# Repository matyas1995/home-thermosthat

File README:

What to do to get OpenThread running

OpenThread now runs in MCUXpresso project (at least the console does).

Next step is to get away from this Eclipse based crap and get the project working under Cmake (so all the way back to start).

MCUXpresso should only be needed to use the clock and peripheral configurators (They make quite a lot of things easier). These will then be just copied over.

The README of the mbedTLS library in the SDK mentions that it has been adapted to use the LTC crypto module of the chip. This should definitely be checked out to use hardware acceleration.

testchange3 for testcommit

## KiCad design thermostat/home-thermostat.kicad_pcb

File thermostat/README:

Errata: gate resistors on GPIO LED drivers missing. Will not pose great problems as long as switching frequency does not get too high to overload MCU pins.

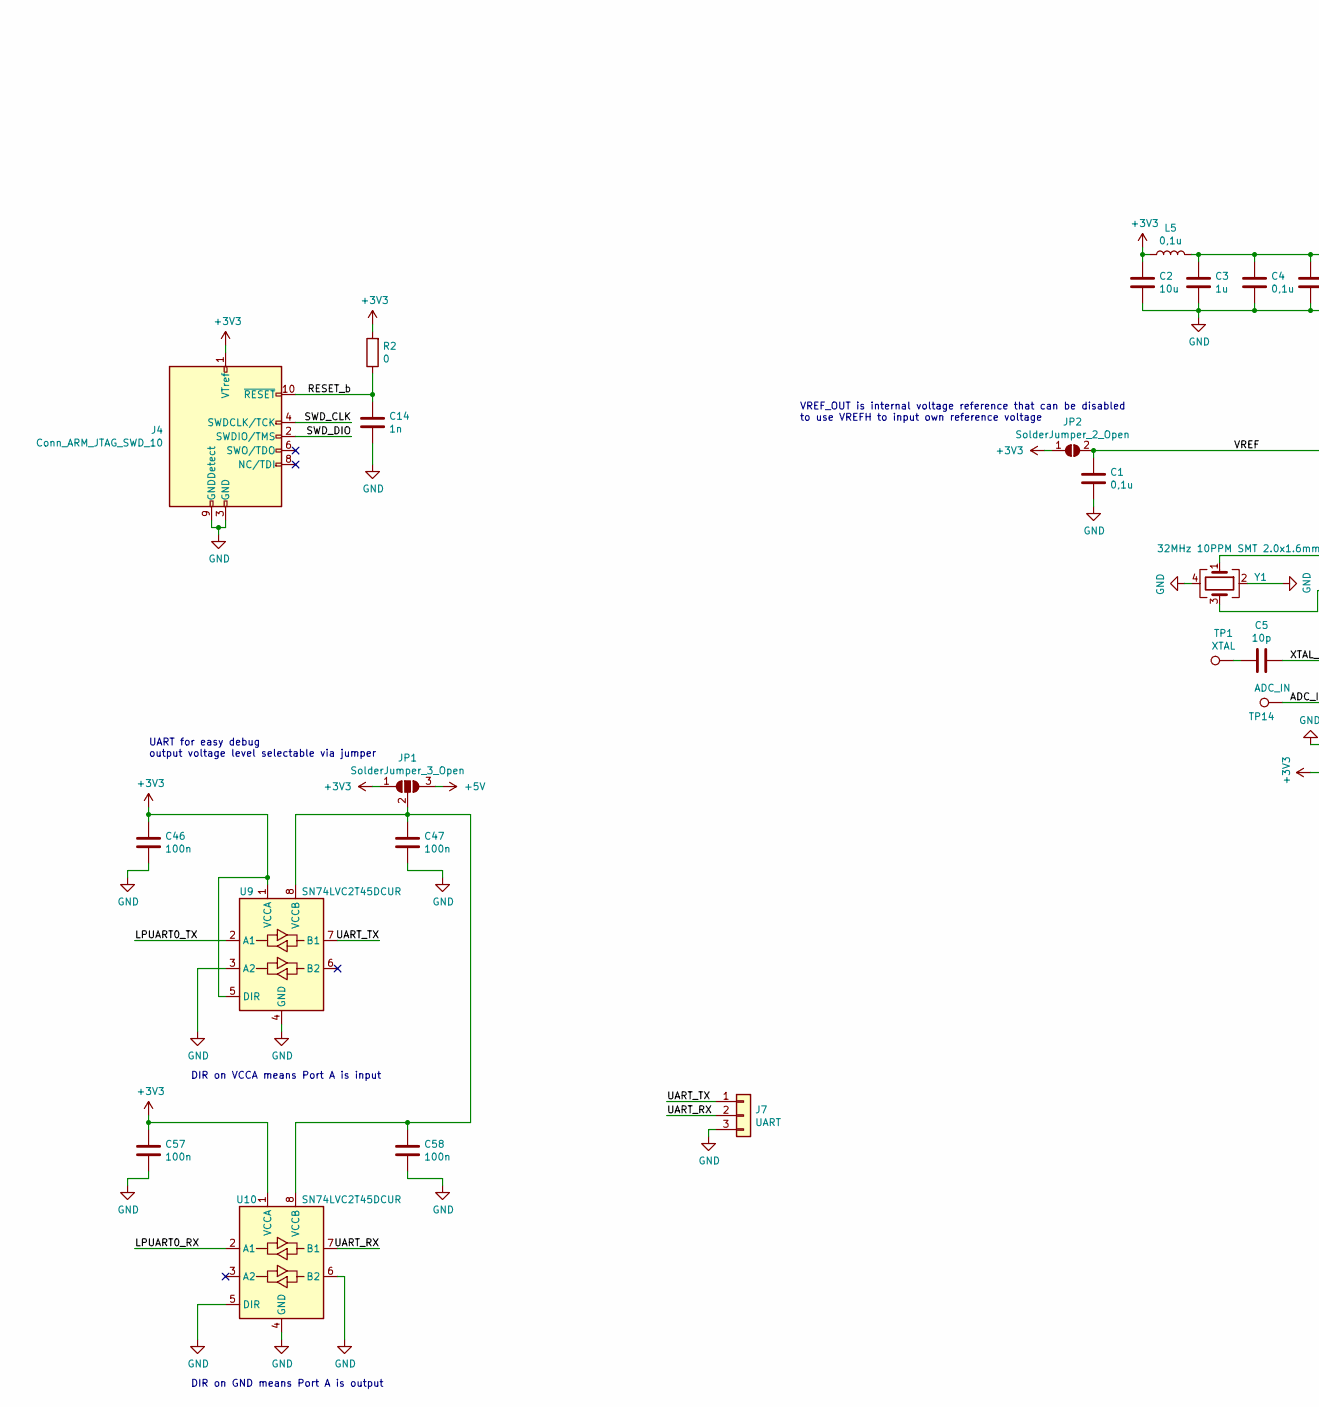
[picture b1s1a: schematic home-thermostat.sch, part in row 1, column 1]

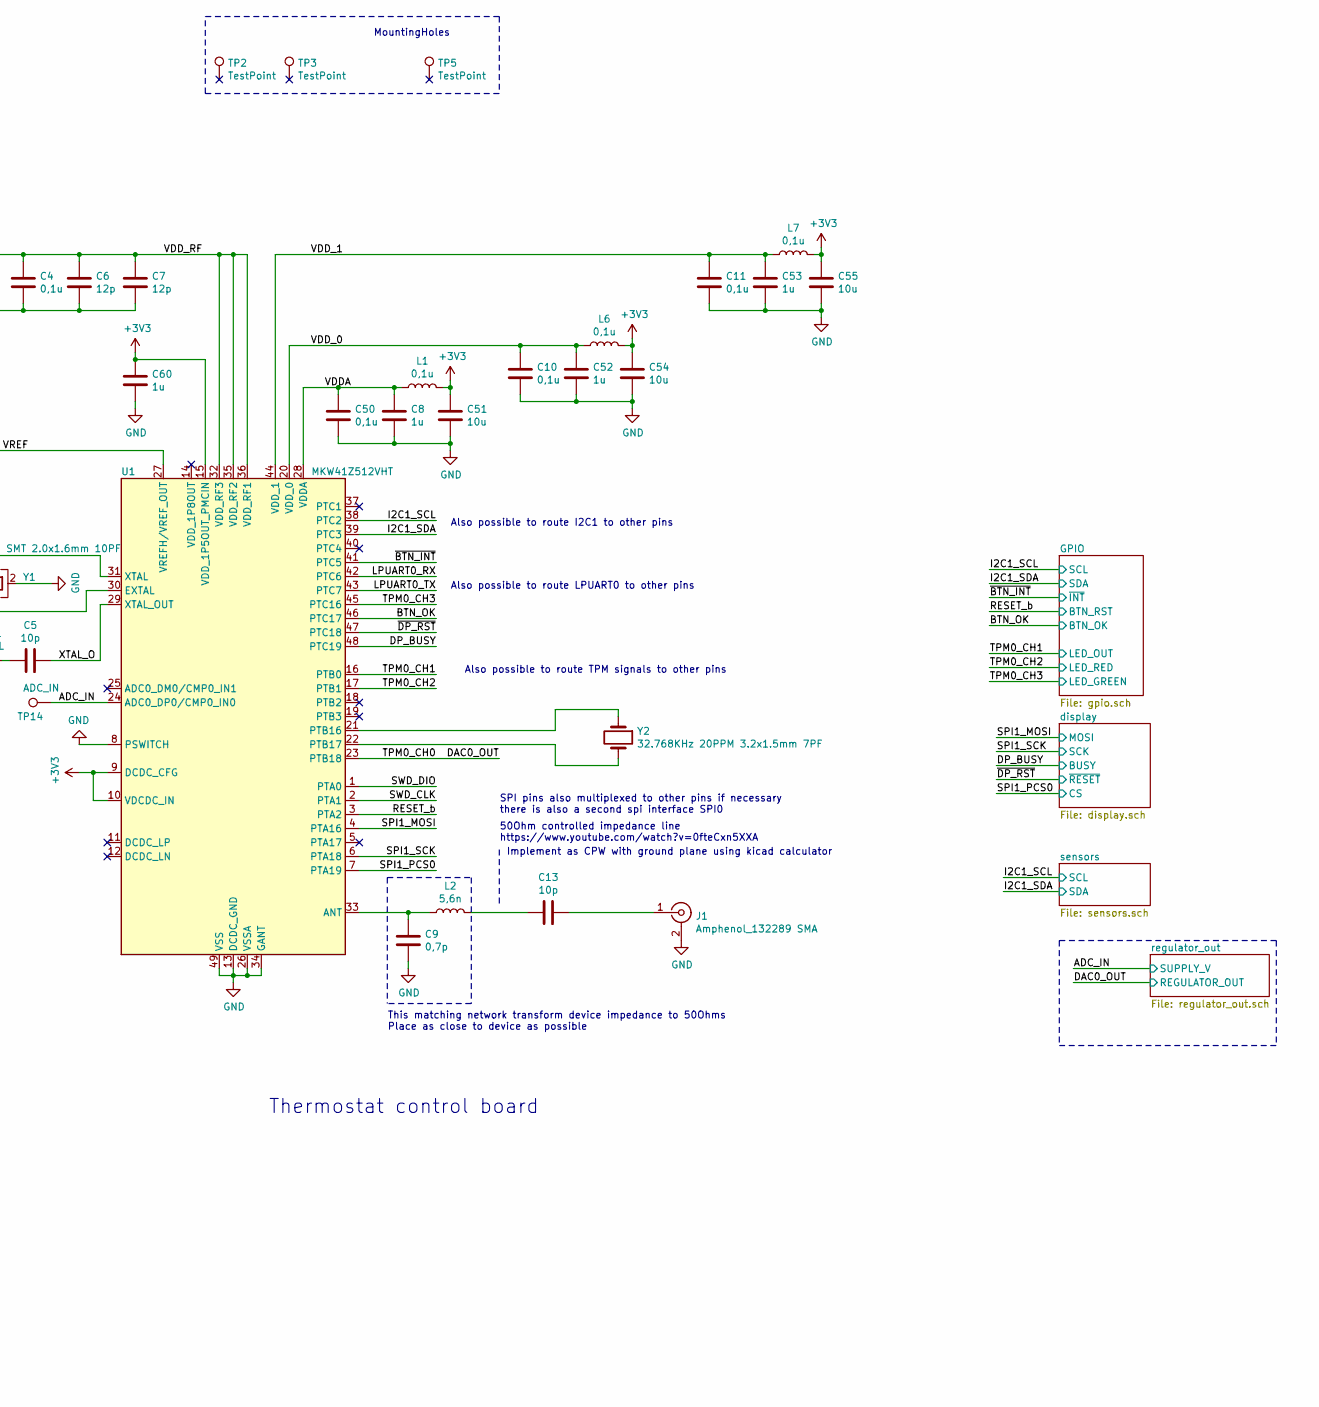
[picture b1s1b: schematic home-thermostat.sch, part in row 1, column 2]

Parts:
C1, C4, C10, C11, C50: 0,1u; C_0402_1005Metric
C2, C51, C54, C55: 10u; C_0603_1608Metric
C3, C8, C52, C53, C60: 1u; C_0402_1005Metric
C5, C13: 10p; C_0402_1005Metric
C6, C7: 12p; C_0402_1005Metric
C9: 0,7p; C_0402_1005Metric
C14: 1n; C_0402_1005Metric
C46, C47, C57, C58: 100n; C_0603_1608Metric
J1: Amphenol_132289 SMA; SMA_Amphenol_132289_EdgeMount
J4: Conn_ARM_JTAG_SWD_10; PinHeader_2x05_P1.27mm_Vertical_SMD
J7: UART; PinHeader_1x03_P2.54mm_Vertical_SMD_Pin1Left
JP1: SolderJumper_3_Open; SolderJumper-3_P1.3mm_Open_Pad1.0x1.5mm
JP2: SolderJumper_2_Open; SolderJumper-2_P1.3mm_Open_Pad1.0x1.5mm
L1, L5, L6, L7: 0,1u; L_0402_1005Metric
L2: 5,6n; L_0402_1005Metric
R2: 0; R_0402_1005Metric
TP1: XTAL; TestPoint_Pad_D1.0mm
TP2, TP3, TP5: TestPoint; MountingHole_3.2mm_M3
TP14: ADC_IN; TestPoint_Pad_D1.0mm
U1: MKW41Z512VHT; NXP_LQFN-48-1EP_7x7mm_P0.5mm_EP3.5x3.5mm_16xMask0.45x0.45
U9, U10: SN74LVC2T45DCUR; VSSOP-8_3.0x3.0mm_P0.65mm
Y1: 32MHz 10PPM SMT 2.0x1.6mm 10PF; Crystal_SMD_2016-4Pin_2.0x1.6mm
Y2: 32.768KHz 20PPM 3.2x1.5mm 7PF; Crystal_SMD_3215-2Pin_3.2x1.5mm

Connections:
+3V3: C2.2, C46.1, C51.2, C54.2, C55.2, C57.1, C60.1, J4.1 (VTref), JP1.1 (A), JP2.1 (A), L1.2, L5.1, L6.2, L7.2, R2.2, U1.9 (DCDC_CFG), U1.10 (VDCDC_IN), U1.15 (VDD_1P5OUT_PMCIN), U9.1 (VCCA), U9.5 (DIR), U10.1 (VCCA); also elsewhere on the board
+5V: JP1.3 (B); also elsewhere on the board
/ADC_IN: TP14.1, U1.24 (ADC0_DP0/CMP0_IN0); also elsewhere on the board
/BTN_OK: U1.46 (PTC17); also elsewhere on the board
/DAC0_OUT: U1.23 (PTB18); also elsewhere on the board
/DP_BUSY: U1.48 (PTC19); also elsewhere on the board
/I2C1_SCL: U1.38 (PTC2); also elsewhere on the board
/I2C1_SDA: U1.39 (PTC3); also elsewhere on the board
/LPUART0_RX: U1.42 (PTC6), U10.2 (A1)
/LPUART0_TX: U1.43 (PTC7), U9.2 (A1)
/RESET_b: C14.1, J4.10 (~RESET~), R2.1, U1.3 (PTA2); also elsewhere on the board
/SPI1_MOSI: U1.4 (PTA16); also elsewhere on the board
/SPI1_PCS0: U1.7 (PTA19); also elsewhere on the board
/SPI1_SCK: U1.6 (PTA18); also elsewhere on the board
/SWD_CLK: J4.4 (SWDCLK/TCK), U1.2 (PTA1)
/SWD_DIO: J4.2 (SWDIO/TMS), U1.1 (PTA0)
/TPM0_CH1: U1.16 (PTB0); also elsewhere on the board
/TPM0_CH2: U1.17 (PTB1); also elsewhere on the board
/TPM0_CH3: U1.45 (PTC16); also elsewhere on the board
/UART_RX: J7.2, U10.7 (B1)
/UART_TX: J7.1, U9.7 (B1)
/VDDA: C8.1, C50.1, L1.1, U1.28 (VDDA)
/VDD_0: C10.1, C52.1, L6.1, U1.20 (VDD_0)
/VDD_1: C11.1, C53.1, L7.1, U1.44 (VDD_1)
/VDD_RF: C3.1, C4.1, C6.1, C7.1, L5.2, U1.32 (VDD_RF3), U1.35 (VDD_RF2), U1.36 (VDD_RF1)
/VREF: C1.1, JP2.2 (B), U1.27 (VREFH/VREF_OUT)
/XTAL_O: C5.1, U1.29 (XTAL_OUT)
/~BTN_INT: U1.41 (PTC5); also elsewhere on the board
/~DP_RST: U1.47 (PTC18); also elsewhere on the board
GND: C1.2, C2.1, C3.2, C4.2, C6.2, C7.2, C8.2, C9.2, C10.2, C11.2, C14.2, C46.2, C47.2, C50.2, C51.1, C52.2, C53.2, C54.1, C55.1, C57.2, C58.2, C60.2, J1.2 (Ext), J4.3 (GND), J4.5 (GND), J4.9 (GNDDetect), J7.3, U1.8 (PSWITCH), U1.13 (DCDC_GND), U1.26 (VSSA), U1.34 (GANT), U1.49 (VSS), U9.3 (A2), U9.4 (GND), U10.4 (GND), U10.5 (DIR), U10.6 (B2), Y1.2, Y1.4; also elsewhere on the board
unnamed: C5.2, TP1.1
unnamed: C9.1, L2.1, U1.33 (ANT)
unnamed: C13.1, J1.1 (In)
unnamed: C13.2, L2.2
unnamed: C47.1, C58.1, JP1.2 (C), U9.8 (VCCB), U10.8 (VCCB)
unnamed: U1.21 (PTB16), Y2.1
unnamed: U1.22 (PTB17), Y2.2
unnamed: U1.30 (EXTAL), Y1.3
unnamed: U1.31 (XTAL), Y1.1

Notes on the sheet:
Thermostat control board
50Ohm controlled impedance line https://www.youtube.com/watch?v=0fteCxn5XXA
Implement as CPW with ground plane using kicad calculator
This matching network transform device impedance to 50Ohms Place as close to device as possible
SPI pins also multiplexed to other pins if necessary there is also a second spi interface SPI0
Also possible to route I2C1 to other pins
Also possible to route LPUART0 to other pins
VREF_OUT is internal voltage reference that can be disabled to use VREFH to input own reference voltage
Also possible to route TPM signals to other pins
MountingHoles
DIR on VCCA means Port A is input
UART for easy debug output voltage level selectable via jumper
DIR on GND means Port A is output

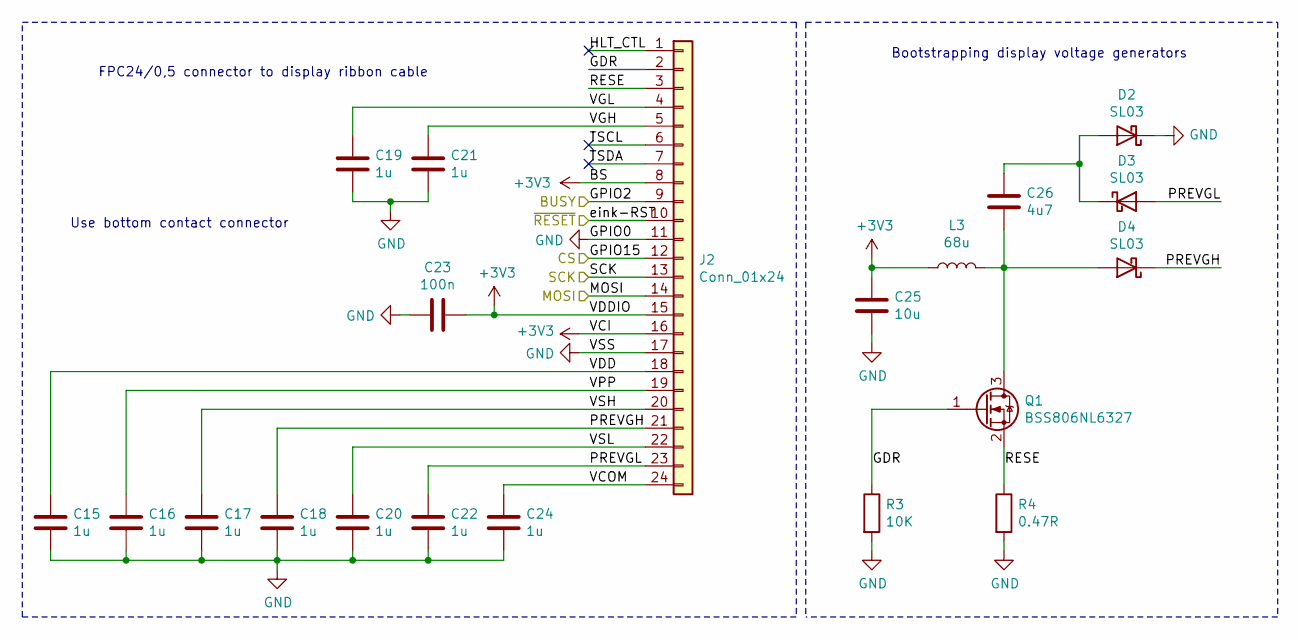
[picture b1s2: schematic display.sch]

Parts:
C15, C16, C17, C18, C19, C20, C21, C22, C24: 1u; C_0603_1608Metric
C23: 100n; C_0603_1608Metric
C25: 10u; C_0603_1608Metric
C26: 4u7; C_0603_1608Metric
D2, D3, D4: SL03; D_SMF
J2: Conn_01x24; TE_2-1734839-4_1x24-1MP_P0.5mm_Horizontal
L3: 68u; L_1210_3225Metric
Q1: BSS806NL6327; SOT-23
R3: 10K; R_0603_1608Metric
R4: 0.47R; R_0603_1608Metric

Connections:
+3V3: C23.2, C25.1, J2.8, J2.15, J2.16, L3.1; also elsewhere on the board
/DP_BUSY: J2.9; also elsewhere on the board
/SPI1_MOSI: J2.14; also elsewhere on the board
/SPI1_PCS0: J2.12; also elsewhere on the board
/SPI1_SCK: J2.13; also elsewhere on the board
/display/GDR: J2.2, Q1.1 (G), R3.1
/display/HLT_CTL: J2.1
/display/PREVGH: C18.1, D4.1 (K), J2.21
/display/PREVGL: C22.1, D3.2 (A), J2.23
/display/RESE: J2.3, Q1.2 (S), R4.1
/display/TSCL: J2.6
/display/TSDA: J2.7
/display/VCOM: C24.1, J2.24
/display/VDD: C15.1, J2.18
/display/VGH: C21.2, J2.5
/display/VGL: C19.2, J2.4
/display/VPP: C16.1, J2.19
/display/VSH: C17.1, J2.20
/display/VSL: C20.1, J2.22
/~DP_RST: J2.10; also elsewhere on the board
GND: C15.2, C16.2, C17.2, C18.2, C19.1, C20.2, C21.1, C22.2, C23.1, C24.2, C25.2, D2.1 (K), J2.11, J2.17, R3.2, R4.2; also elsewhere on the board
unnamed: C26.1, D2.2 (A), D3.1 (K)
unnamed: C26.2, D4.2 (A), L3.2, Q1.3 (D)

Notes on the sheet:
FPC24/0,5 connector to display ribbon cable
Bootstrapping display voltage generators
Use bottom contact connector

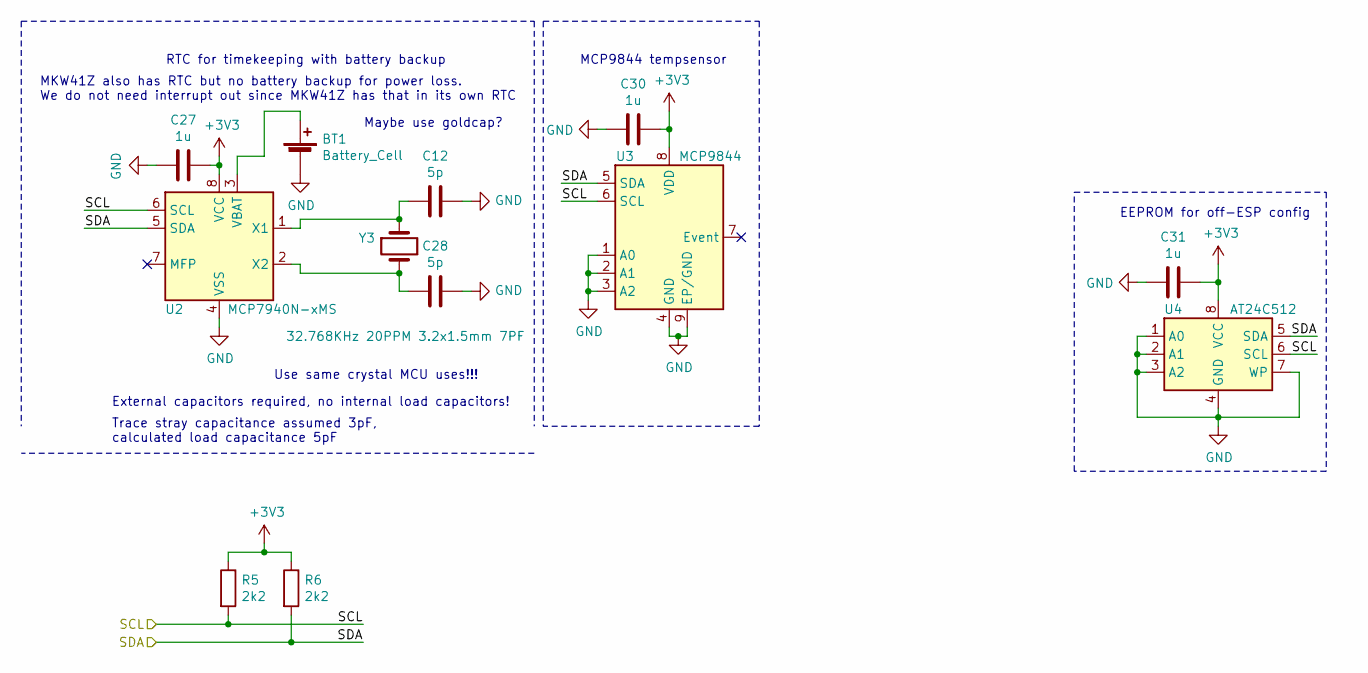
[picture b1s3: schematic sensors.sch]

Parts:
BT1: Battery_Cell; BatteryHolder_Keystone_3002_1x2032
C12, C28: 5p; C_0603_1608Metric
C27, C30, C31: 1u; C_0603_1608Metric
R5, R6: 2k2; R_0603_1608Metric
U2: MCP7940N-xMS; MSOP-8_3x3mm_P0.65mm
U3: MCP9844; DFN-8-1EP_3x2mm_P0.5mm_EP1.36x1.46mm
U4: AT24C512; DIP-8_W7.62mm_SMDSocket_SmallPads
Y3: 32.768KHz 20PPM 3.2x1.5mm 7PF; Crystal_SMD_3215-2Pin_3.2x1.5mm

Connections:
+3V3: C27.1, C30.1, C31.1, R5.1, R6.1, U2.8 (VCC), U3.8 (VDD), U4.8 (VCC); also elsewhere on the board
/I2C1_SCL: R5.2, U2.6 (SCL), U3.6 (SCL), U4.6 (SCL); also elsewhere on the board
/I2C1_SDA: R6.2, U2.5 (SDA), U3.5 (SDA), U4.5 (SDA); also elsewhere on the board
GND: BT1.2 (-), C12.1, C27.2, C28.1, C30.2, C31.2, U2.4 (VSS), U3.1 (A0), U3.2 (A1), U3.3 (A2), U3.4 (GND), U3.9 (EP/GND), U4.1 (A0), U4.2 (A1), U4.3 (A2), U4.4 (GND), U4.7 (WP); also elsewhere on the board
unnamed: BT1.1 (+), U2.3 (VBAT)
unnamed: C12.2, U2.1 (X1), Y3.1
unnamed: C28.2, U2.2 (X2), Y3.2

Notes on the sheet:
RTC for timekeeping with battery backup
Maybe use goldcap?
MCP9844 tempsensor
MKW41Z also has RTC but no battery backup for power loss. We do not need interrupt out since MKW41Z has that in its own RTC
EEPROM for off-ESP config
Use same crystal MCU uses!!!
External capacitors required, no internal load capacitors!
Trace stray capacitance assumed 3pF, calculated load capacitance 5pF

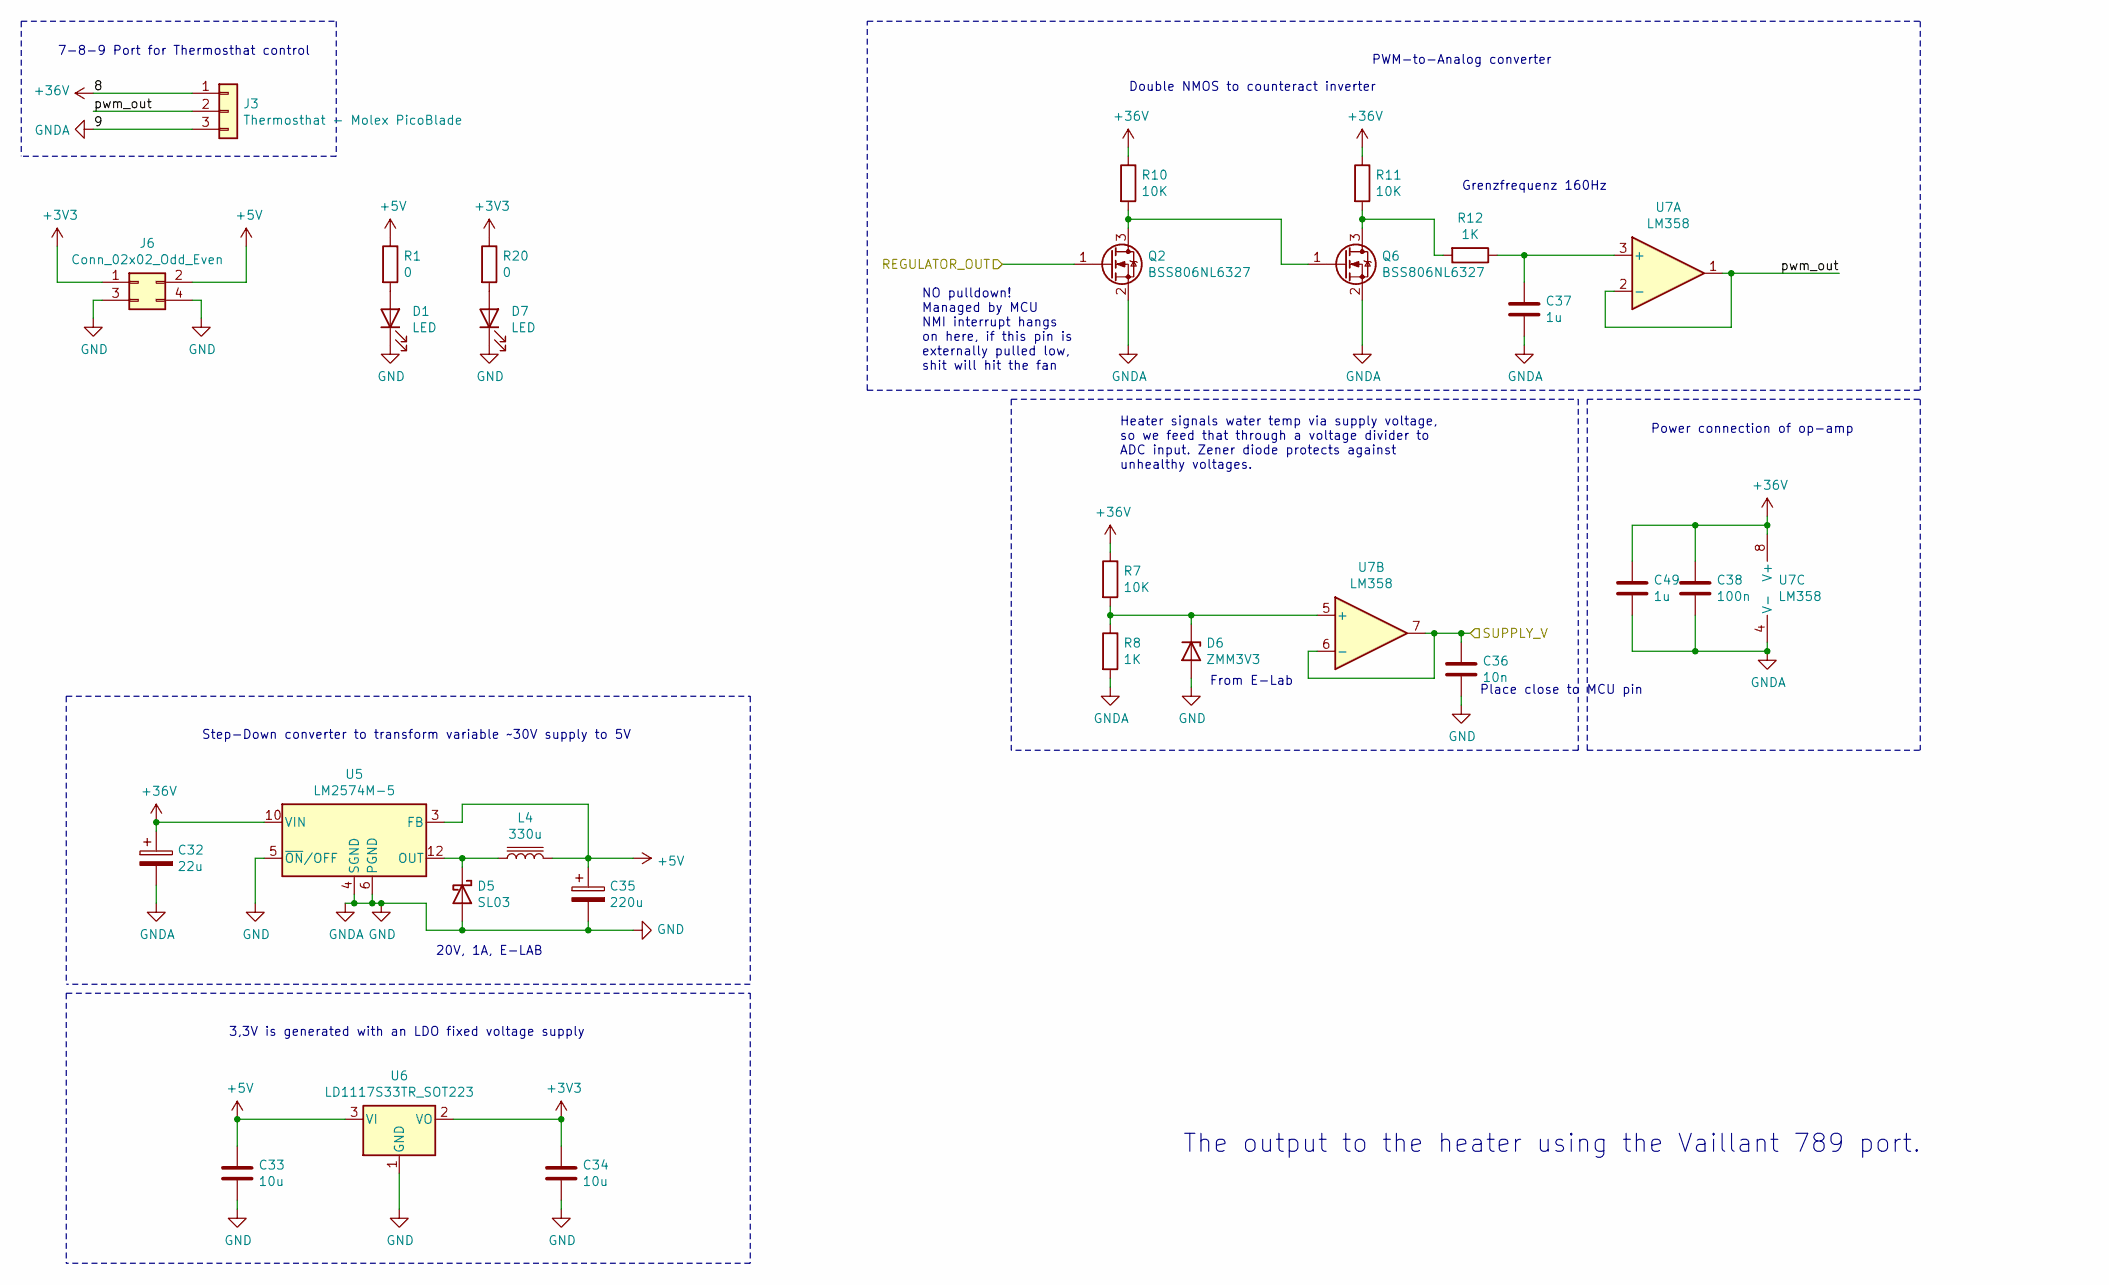
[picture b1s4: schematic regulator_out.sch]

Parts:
C32: 22u; CP_Elec_6.3x3
C33, C34: 10u; C_0603_1608Metric
C35: 220u; CP_Elec_6.3x5.4
C36: 10n; C_0402_1005Metric
C37, C49: 1u; C_0603_1608Metric
C38: 100n; C_0603_1608Metric
D1, D7: LED; LED_1210_3225Metric
D5: SL03; D_SMF
D6: ZMM3V3; D_MiniMELF
J3: Thermosthat - Molex PicoBlade; PinHeader_1x03_P2.54mm_Vertical_SMD_Pin1Left
J6: Conn_02x02_Odd_Even; PinHeader_2x02_P2.54mm_Vertical_SMD
L4: 330u; L_7.3x7.3_H3.5
Q2, Q6: BSS806NL6327; SOT-23
R1, R20: 0; R_0603_1608Metric
R7, R10, R11: 10K; R_0603_1608Metric
R8, R12: 1K; R_0603_1608Metric
U5: LM2574M-5; SOIC-14W_7.5x9mm_P1.27mm
U6: LD1117S33TR_SOT223; SOT-223-3_TabPin2
U7: LM358; SOIC-8_3.9x4.9mm_P1.27mm

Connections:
+3V3: C34.1, J6.1, R20.1, U6.2 (VO); also elsewhere on the board
+5V: C33.1, C35.1, J6.2, L4.2, R1.1, U5.3 (FB), U6.3 (VI); also elsewhere on the board
+36V: C32.1, C38.1, C49.1, J3.1, R7.1, R10.1, R11.1, U5.10 (VIN), U7.8 (V+)
/ADC_IN: C36.1, U7.6 (-), U7.7; also elsewhere on the board
/DAC0_OUT: Q2.1 (G); also elsewhere on the board
/regulator_out/pwm_out: J3.2, U7.1, U7.2 (-)
GND: C32.2, C33.2, C34.2, C35.2, C36.2, C37.2, C38.2, C49.2, D1.1 (K), D5.2 (A), D6.2 (A), D7.1 (K), J3.3, J6.3, J6.4, Q2.2 (S), Q6.2 (S), R8.2, U5.4 (SGND), U5.5 (~ON~/OFF), U5.6 (PGND), U6.1 (GND), U7.4 (V-); also elsewhere on the board
unnamed: C37.1, R12.1, U7.3 (+)
unnamed: D1.2 (A), R1.2
unnamed: D5.1 (K), L4.1, U5.12 (OUT)
unnamed: D6.1 (K), R7.2, R8.1, U7.5 (+)
unnamed: D7.2 (A), R20.2
unnamed: Q2.3 (D), Q6.1 (G), R10.2
unnamed: Q6.3 (D), R11.2, R12.2

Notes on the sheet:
The output to the heater using the Vaillant 789 port.
Power connection of op-amp
From E-Lab
Heater signals water temp via supply voltage, so we feed that through a voltage divider to ADC input. Zener diode protects against unhealthy voltages.
Grenzfrequenz 160Hz
PWM-to-Analog converter
7-8-9 Port for Thermosthat control
20V, 1A, E-LAB
Step-Down converter to transform variable ~~30V supply to 5V
3,3V is generated with an LDO fixed voltage supply
Place close to MCU pin
Double NMOS to counteract inverter
NO pulldown! Managed by MCU NMI interrupt hangs on here, if this pin is externally pulled low, shit will hit the fan

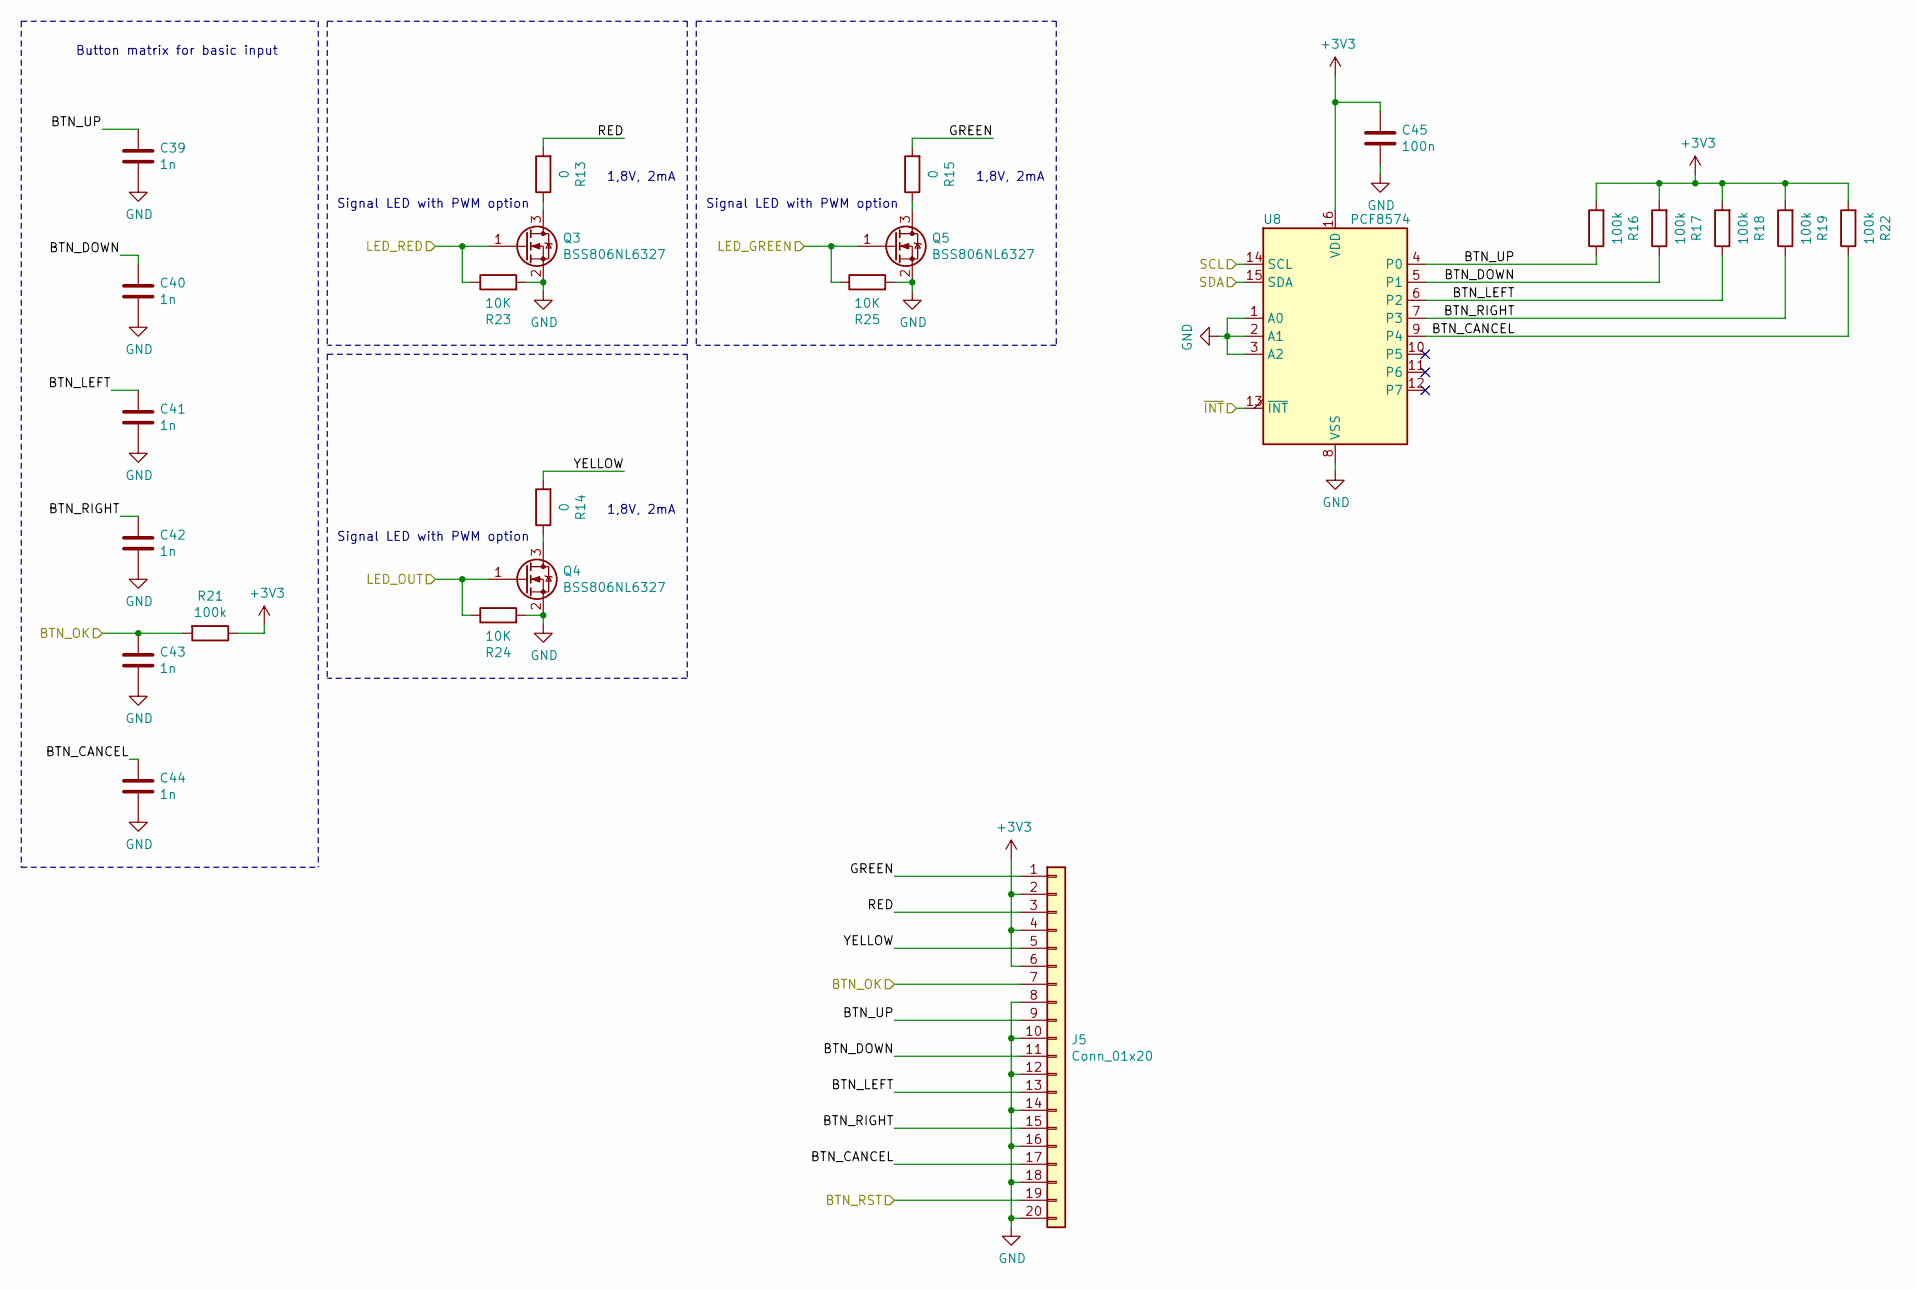
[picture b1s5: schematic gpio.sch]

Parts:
C39, C40, C41, C42, C43, C44: 1n; C_0402_1005Metric
C45: 100n; C_0603_1608Metric
J5: Conn_01x20; PinHeader_2x10_P2.54mm_Vertical_SMD
Q3, Q4, Q5: BSS806NL6327; SOT-23
R13, R14, R15: 0; R_0603_1608Metric
R16, R17, R18, R19, R21, R22: 100k; R_0402_1005Metric
R23, R24, R25: 10K; R_0402_1005Metric
U8: PCF8574; SOIC-16W_7.5x10.3mm_P1.27mm

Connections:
+3V3: C45.1, J5.2, J5.4, J5.6, R16.2, R17.2, R18.2, R19.2, R21.1, R22.2, U8.16 (VDD); also elsewhere on the board
/BTN_OK: C43.1, J5.7, R21.2; also elsewhere on the board
/GPIO/BTN_CANCEL: C44.1, J5.17, R22.1, U8.9 (P4)
/GPIO/BTN_DOWN: C40.1, J5.11, R17.1, U8.5 (P1)
/GPIO/BTN_LEFT: C41.1, J5.13, R18.1, U8.6 (P2)
/GPIO/BTN_RIGHT: C42.1, J5.15, R19.1, U8.7 (P3)
/GPIO/BTN_UP: C39.1, J5.9, R16.1, U8.4 (P0)
/GPIO/GREEN: J5.1, R15.2
/GPIO/RED: J5.3, R13.2
/GPIO/YELLOW: J5.5, R14.2
/I2C1_SCL: U8.14 (SCL); also elsewhere on the board
/I2C1_SDA: U8.15 (SDA); also elsewhere on the board
/RESET_b: J5.19; also elsewhere on the board
/TPM0_CH1: Q4.1 (G), R24.1; also elsewhere on the board
/TPM0_CH2: Q3.1 (G), R23.1; also elsewhere on the board
/TPM0_CH3: Q5.1 (G), R25.1; also elsewhere on the board
/~BTN_INT: U8.13 (~INT~); also elsewhere on the board
GND: C39.2, C40.2, C41.2, C42.2, C43.2, C44.2, C45.2, J5.8, J5.10, J5.12, J5.14, J5.16, J5.18, J5.20, Q3.2 (S), Q4.2 (S), Q5.2 (S), R23.2, R24.2, R25.2, U8.1 (A0), U8.2 (A1), U8.3 (A2), U8.8 (VSS); also elsewhere on the board
unnamed: Q3.3 (D), R13.1
unnamed: Q4.3 (D), R14.1
unnamed: Q5.3 (D), R15.1

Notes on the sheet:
Button matrix for basic input
Signal LED with PWM option
1,8V, 2mA

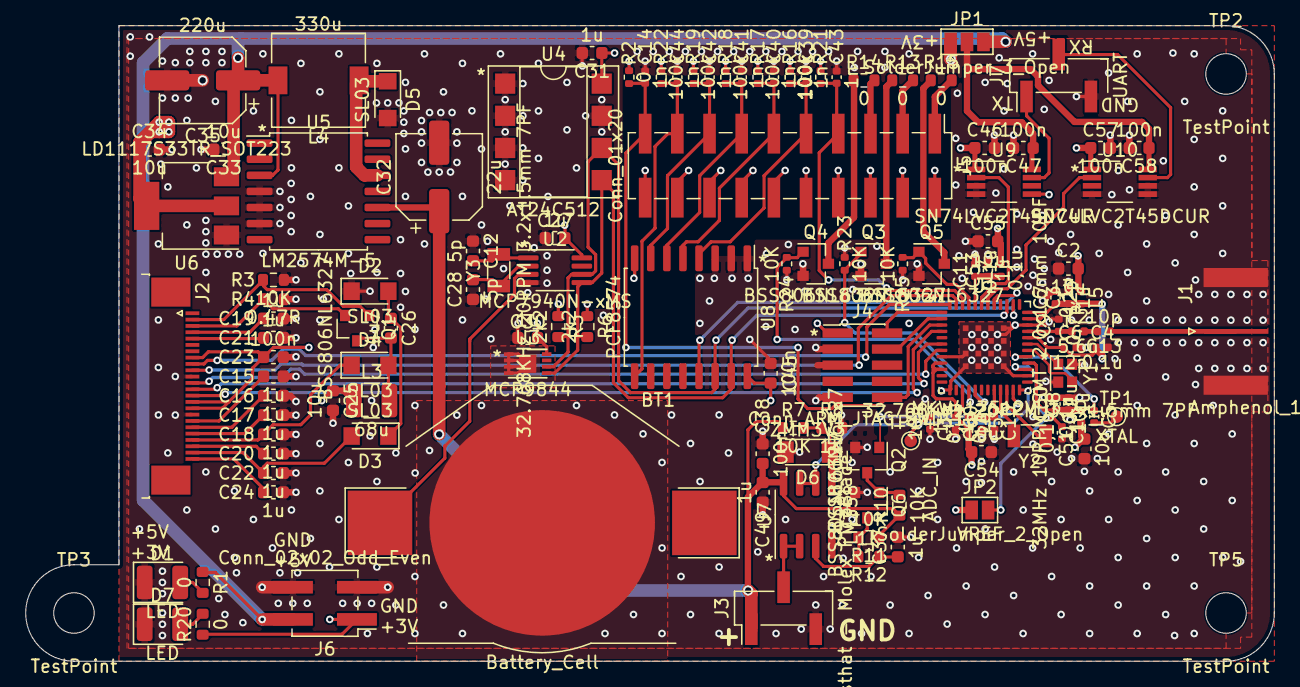
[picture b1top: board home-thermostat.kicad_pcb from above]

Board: 4 copper layers, 98.6 x 50.2 mm, 128 parts (0 on the bottom side), 75 nets.

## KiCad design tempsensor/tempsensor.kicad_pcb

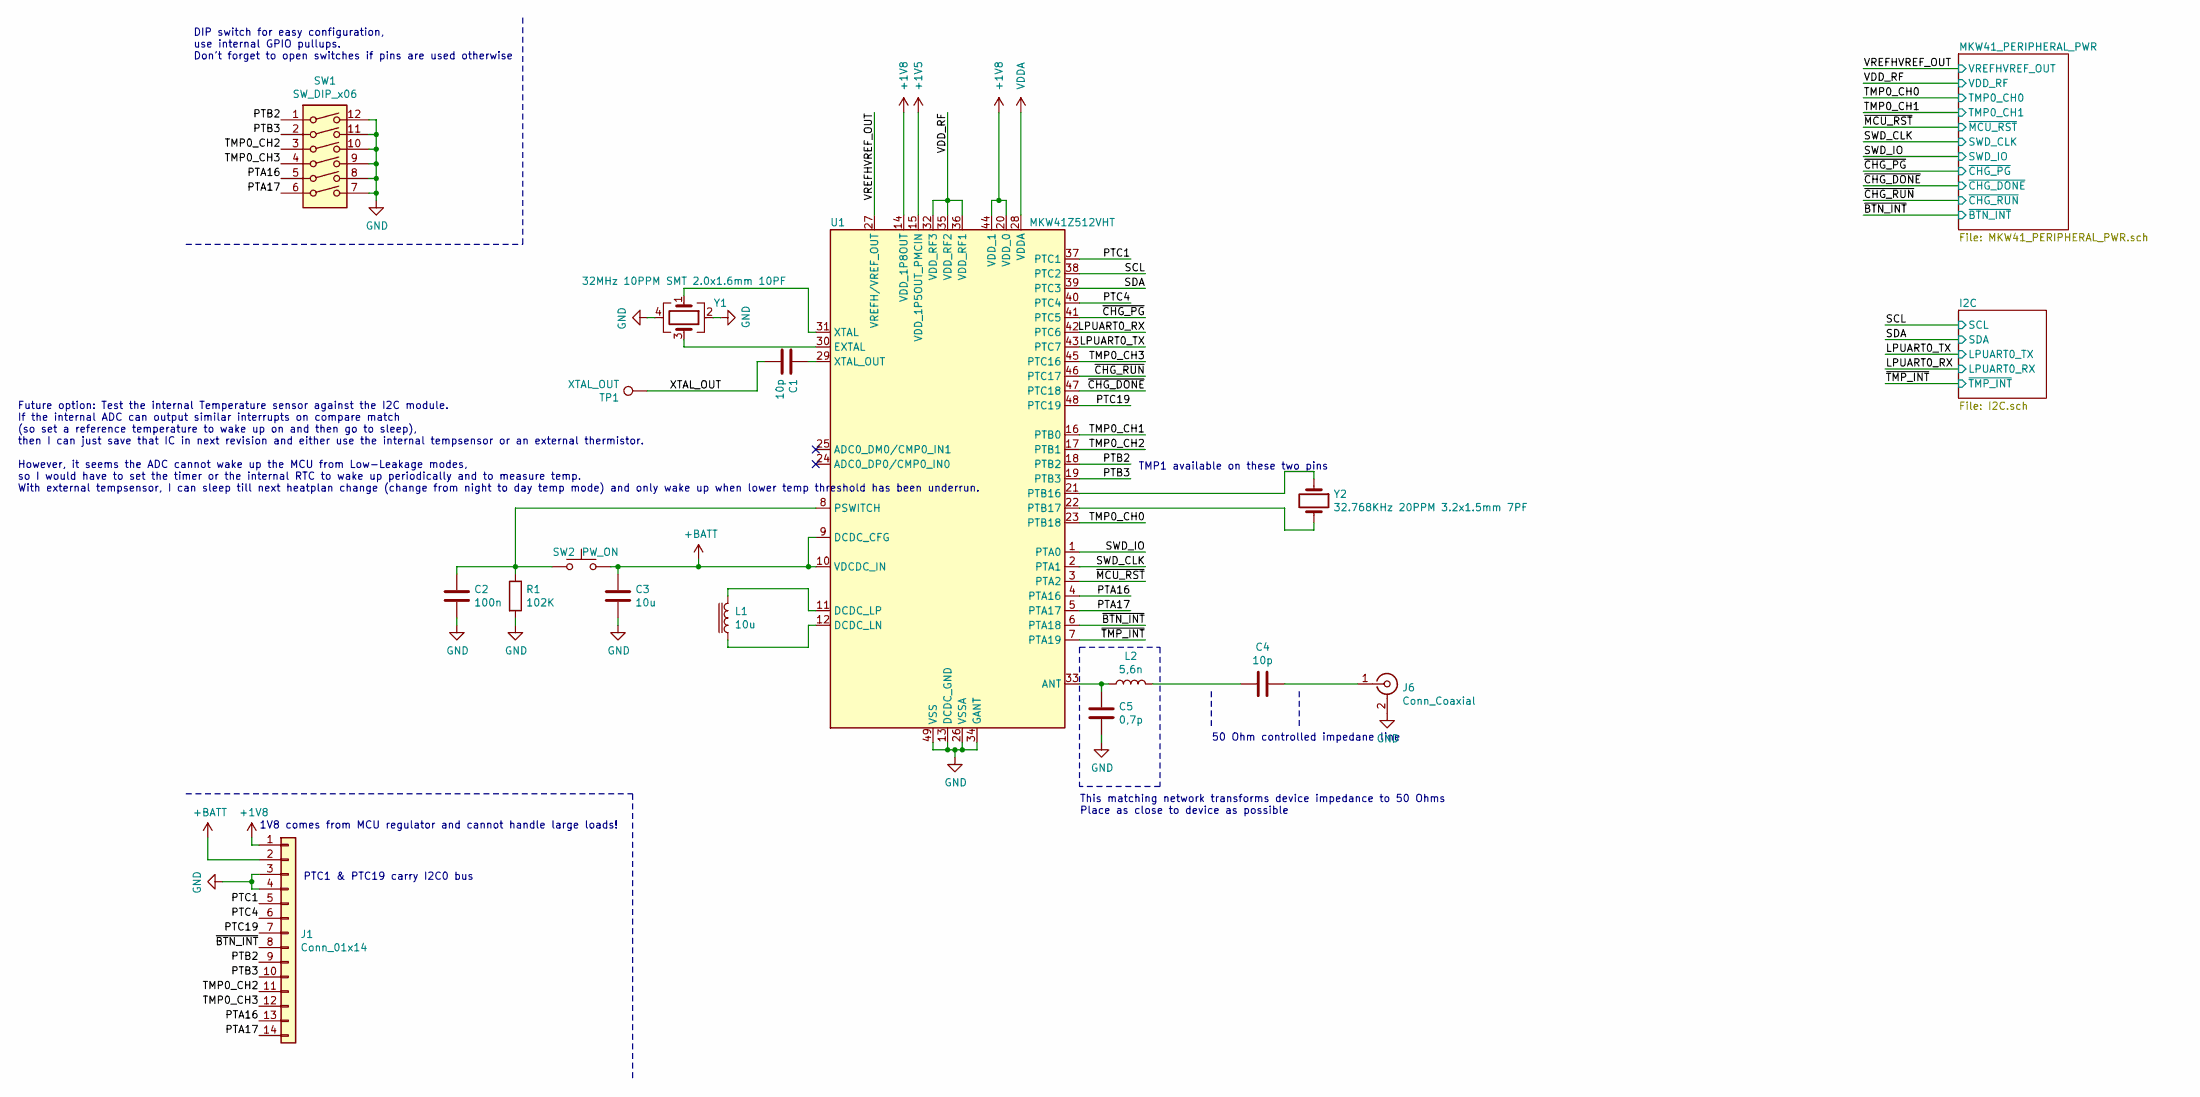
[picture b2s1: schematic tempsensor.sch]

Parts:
C1, C4: 10p; C_0402_1005Metric
C2: 100n; C_0402_1005Metric
C3: 10u; C_0603_1608Metric
C5: 0,7p; C_0402_1005Metric
J1: Conn_01x14; PinHeader_2x07_P2.54mm_Vertical
J6: Conn_Coaxial; SMA_Amphenol_132289_EdgeMount
L1: 10u; L_Wuerth_MAPI-3012
L2: 5,6n; L_0402_1005Metric
R1: 102K; R_0402_1005Metric
SW1: SW_DIP_x06; SW_DIP_SPSTx06_Slide_Omron_A6S-610x_W8.9mm_P2.54mm
SW2: PW_ON; SW_PUSH_6mm_H5mm
TP1: XTAL_OUT; TestPoint_Pad_D1.0mm
U1: MKW41Z512VHT; NXP_LQFN-48-1EP_7x7mm_P0.5mm_EP3.5x3.5mm_16xMask0.45x0.45
Y1: 32MHz 10PPM SMT 2.0x1.6mm 10PF; Crystal_SMD_2016-4Pin_2.0x1.6mm
Y2: 32.768KHz 20PPM 3.2x1.5mm 7PF; Crystal_SMD_3215-2Pin_3.2x1.5mm

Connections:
+1V5: U1.15 (VDD_1P5OUT_PMCIN); also elsewhere on the board
+1V8: J1.1, U1.14 (VDD_1P8OUT), U1.20 (VDD_0), U1.44 (VDD_1); also elsewhere on the board
+BATT: C3.1, J1.2, SW2.2, U1.9 (DCDC_CFG), U1.10 (VDCDC_IN); also elsewhere on the board
/LPUART0_RX: U1.42 (PTC6); also elsewhere on the board
/LPUART0_TX: U1.43 (PTC7); also elsewhere on the board
/PTA16: J1.13, SW1.5, U1.4 (PTA16)
/PTA17: J1.14, SW1.6, U1.5 (PTA17)
/PTB2: J1.9, SW1.1, U1.18 (PTB2)
/PTB3: J1.10, SW1.2, U1.19 (PTB3)
/PTC1: J1.5, U1.37 (PTC1)
/PTC4: J1.6, U1.40 (PTC4)
/PTC19: J1.7, U1.48 (PTC19)
/SCL: U1.38 (PTC2); also elsewhere on the board
/SDA: U1.39 (PTC3); also elsewhere on the board
/SWD_CLK: U1.2 (PTA1); also elsewhere on the board
/SWD_IO: U1.1 (PTA0); also elsewhere on the board
/TMP0_CH0: U1.23 (PTB18); also elsewhere on the board
/TMP0_CH1: U1.16 (PTB0); also elsewhere on the board
/TMP0_CH2: J1.11, SW1.3, U1.17 (PTB1)
/TMP0_CH3: J1.12, SW1.4, U1.45 (PTC16)
/VDD_RF: U1.32 (VDD_RF3), U1.35 (VDD_RF2), U1.36 (VDD_RF1); also elsewhere on the board
/VREFHVREF_OUT: U1.27 (VREFH/VREF_OUT); also elsewhere on the board
/XTAL_OUT: C1.2, TP1.1
/~BTN_INT: J1.8, U1.6 (PTA18); also elsewhere on the board
/~CHG_DONE: U1.47 (PTC18); also elsewhere on the board
/~CHG_PG: U1.41 (PTC5); also elsewhere on the board
/~CHG_RUN: U1.46 (PTC17); also elsewhere on the board
/~MCU_RST: U1.3 (PTA2); also elsewhere on the board
/~TMP_INT: U1.7 (PTA19); also elsewhere on the board
GND: C2.2, C3.2, C5.2, J1.3, J1.4, J6.2 (Ext), R1.2, SW1.7, SW1.8, SW1.9, SW1.10, SW1.11, SW1.12, U1.13 (DCDC_GND), U1.26 (VSSA), U1.34 (GANT), U1.49 (VSS), Y1.2, Y1.4; also elsewhere on the board
unnamed: C1.1, U1.29 (XTAL_OUT)
unnamed: C2.1, R1.1, SW2.1, U1.8 (PSWITCH)
unnamed: C4.1, J6.1 (In)
unnamed: C4.2, L2.2
unnamed: C5.1, L2.1, U1.33 (ANT)
unnamed: L1.1, U1.12 (DCDC_LN)
unnamed: L1.2, U1.11 (DCDC_LP)
unnamed: U1.21 (PTB16), Y2.1
unnamed: U1.22 (PTB17), Y2.2
unnamed: U1.30 (EXTAL), Y1.3
unnamed: U1.31 (XTAL), Y1.1
VDDA: U1.28 (VDDA); also elsewhere on the board

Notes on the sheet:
This matching network transforms device impedance to 50 Ohms Place as close to device as possible
50 Ohm controlled impedane line
TMP1 available on these two pins
PTC1 & PTC19 carry I2C0 bus
DIP switch for easy configuration, use internal GPIO pullups. Don't forget to open switches if pins are used otherwise
1V8 comes from MCU regulator and cannot handle large loads!
Future option: Test the internal Temperature sensor against the I2C module. If the internal ADC can output similar interrupts on compare match (so set a reference temperature to wake up on and then go to sleep), then I can just save that IC in next revision and either use the internal tempsensor or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
